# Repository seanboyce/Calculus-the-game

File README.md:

# Introduction
An electronic strategy board game about mining an asteroid and barter. It is also fully compatible with Settlers of Catan. So if you already own that game, you can play it using this board if you wish (using the cards and pieces from the original). The holders of the Catan copyright also generously allow you to make one (1) handmade copy of their game for personal use. A practical thing to do is buy their game, and use the included pieces and cards (although please note the pieces will only physically fit the full-size version, see below). For more information on IP, please visit this link: https://www.catan.com/guidelines-dealing-intellectual-property-catan

Out of respect for their IP (and also for fun), my own game will be sci-fi themed and will not use or refer to their IP beyond this point. 

## Sci-Fi theme?
The name of the game is Calculus, in the sense of a "stone, or concretion of material". In this case, an asteroid in deep space! You are one of up to four corporations that are racing to exploit this valuable asteroid. The corporation that reaches a certain level of development (10 Infrastructure Points) first will own this tiny piece of the sky. This is the object of the game. Besides the four corporations, a mysterious hacker has made their home here, and is bound to interfere with your plans...

(for more information, read the short, bewildering manual)

# Status
The electronics and firmware are in a finished state. Game and reference cards exist and are usable, but the design is nothing special. The game manual is an A5 saddle-stitched booklet, available as a pre-imposed, print-ready document. If you want to help, please redesign my print materials. You are very likely better at this than I am.

There are two versions of this game, both complete:

1. The cheap version (about USD 15.00 to manufacture 1 unit in Asia) -- this version only has one PCB, although you will need 3 units to build the game. It is very cheap to manufacture, but a bit small and cramped to play. Call it a "travel version"! It is missing a little polish overall, and the firmware (while completely functional) is a little chaotic. Notably, trade ports are not electronic (I use magnetic discs), the landing zone (unproductive tile) is limited to being in the center of the board, and there's no MCU on the board itself -- it needs to be added externally and wired in to the inputs. You'll also need to hack in a button. Still, it's very cheap to make and perfectly cromulent.
2. The full-size version (about USD 37.50 to manufacture 1 unit in Asia) -- this one is *much larger* (more than double the size). It uses two PCBs: a large one (you will need 3), and a small one (you will need 1). The small PCB has space for an MCU, making the final board much more self-contained. The small board goes in the center and is also an active game tile -- the landing zone (unproductive tile) can be randomized like other tiles because of this. Trade ports are randomized and represented by RGB LEDs like resource tiles (or off for 3:1). There are also some cosmetic improvements like a proper button and nicer lines. I've also substantially cleaned up the firmware to control all those LEDs -- there are 388 (!) LEDs on the board when you count up all the RGB LEDs and two digit 8-segment displays. 

Other than noted above, both versions play the same. 

## Power
It's expected that you power the game via a USB battery bank. Like the kind you use to recharge phones. However, you can power it from any USB port or 5V source. Current consumption at 5v should be around 250mA for the cheap version, and a little higher for the full version (say 300mA).

Note that some power banks will automatically turn off if the power draw is too low. When pressing the 'next turn' button, the power draw can dip below this threshold, causing the game to turn off and lose it's state! To avoid this, some power banks have a 'low current mode' that disables this feature -- check your powerbank manual.

An alternative solution is to put a resistor across power and ground to increase the current draw. A 100 ohm resistor was sufficient in my case. This adds 50mA to the current consumption, but still keeps it low enough that my power bank will run the game for 30 hours or so per charge.

Building your own rechargeable power supply, or powering it from a phone charger instead of a battery are also reasonable solutions!

## CPU
The cheap version of the game can use more or less any RP2040 based board. The original Pi Pico works fine. The full version specifically requires the XIAO RP2040 -- it's smaller and I needed the space.

## Structural
The boards for the cheap version are intended to be attached above a small project box or similar. This serves the dual purpose of housing a microcontroller, and fixing the 3 PCBs firmly in place. The larger board has all those electronics integrated, and is meant to be bolted to something rigid. I use a circular bamboo serving tray, this leaves a hollow space under the board suitable for storing pieces, the power supply, and the manual.

You can also just add rubber feet to the PCB, the type that are used for furniture and attach on via M3 bolts. This will let you rest it on most flat sufaces. These should be at least 8mm high for proper clearance, I found 10mm more practical. The benefit of this approach is that you can 'stack' the 3 big PCBs, and store the game in a smaller box. On the other hand, it offers no strain relief on the cabling (which can get a bit tangled). I found that bolting it to a rigid surface was much more practical.

## Game Pieces
The cheap requires custom pieces -- hex spacers, bolts, and nuts colored with a permanent marker work fine. The full size board can be played with pieces from a Catan set, or you can make your own.

I like the weight of metal game pieces -- so I dyed 25mm brass hex spacers as the 'tunnels', dyed M6 nuts as the 'mines', and add a ~13mm dyed M6 bolt to them to upgrade them to 'drills'.

To dye these metal pieces, colored permanent marker worked really well.

# Firmware
Besides the assembled PCBs, you will need to load firmware to the main microcontroller (an RP2040). This is pretty easy and can be done over USB. The firmware is heavily commented -- this is so you can make 'house' modifications to the game mechanics, to change the rules if you want. You could even design a completely new game!

# Notes on Assembly
Assembling the PCBs will require that you are comfortable with surface-mount soldering. It's not nearly as hard as it looks. You'll need solder paste and a hot air rework station though. If you don't have these, check if there's a hackerspace near you. They probably will! The default designs use 0402 (1005 metric) components. If you want something easier to solder, look for the 0603 version of the kicad and production files in the fullsize board directory. 

# Having Trouble? Something Confusing?
Raise an issue here on Github. I check in from time to time and will likely respond.

# Image of Completed Board (full version)

# Image of Completed Board (cheap version)

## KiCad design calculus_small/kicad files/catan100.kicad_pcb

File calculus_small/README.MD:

# Pieces
For this game size, brass hex spacers, bolts, and nuts work really well.

- Hex spacers are 'tunnels'
- Nuts are 'mines'
- Nuts with a bolt slightly screwed in are 'drills'

If you color them with permanent marker, they look quite nice.

# Routing
Yeah, the routing on this board is very YOLO. Feel free to make improvements. I have only a few hours of free time per week so optimized for getting the thing done.

# Notes
The production files are in metric units.

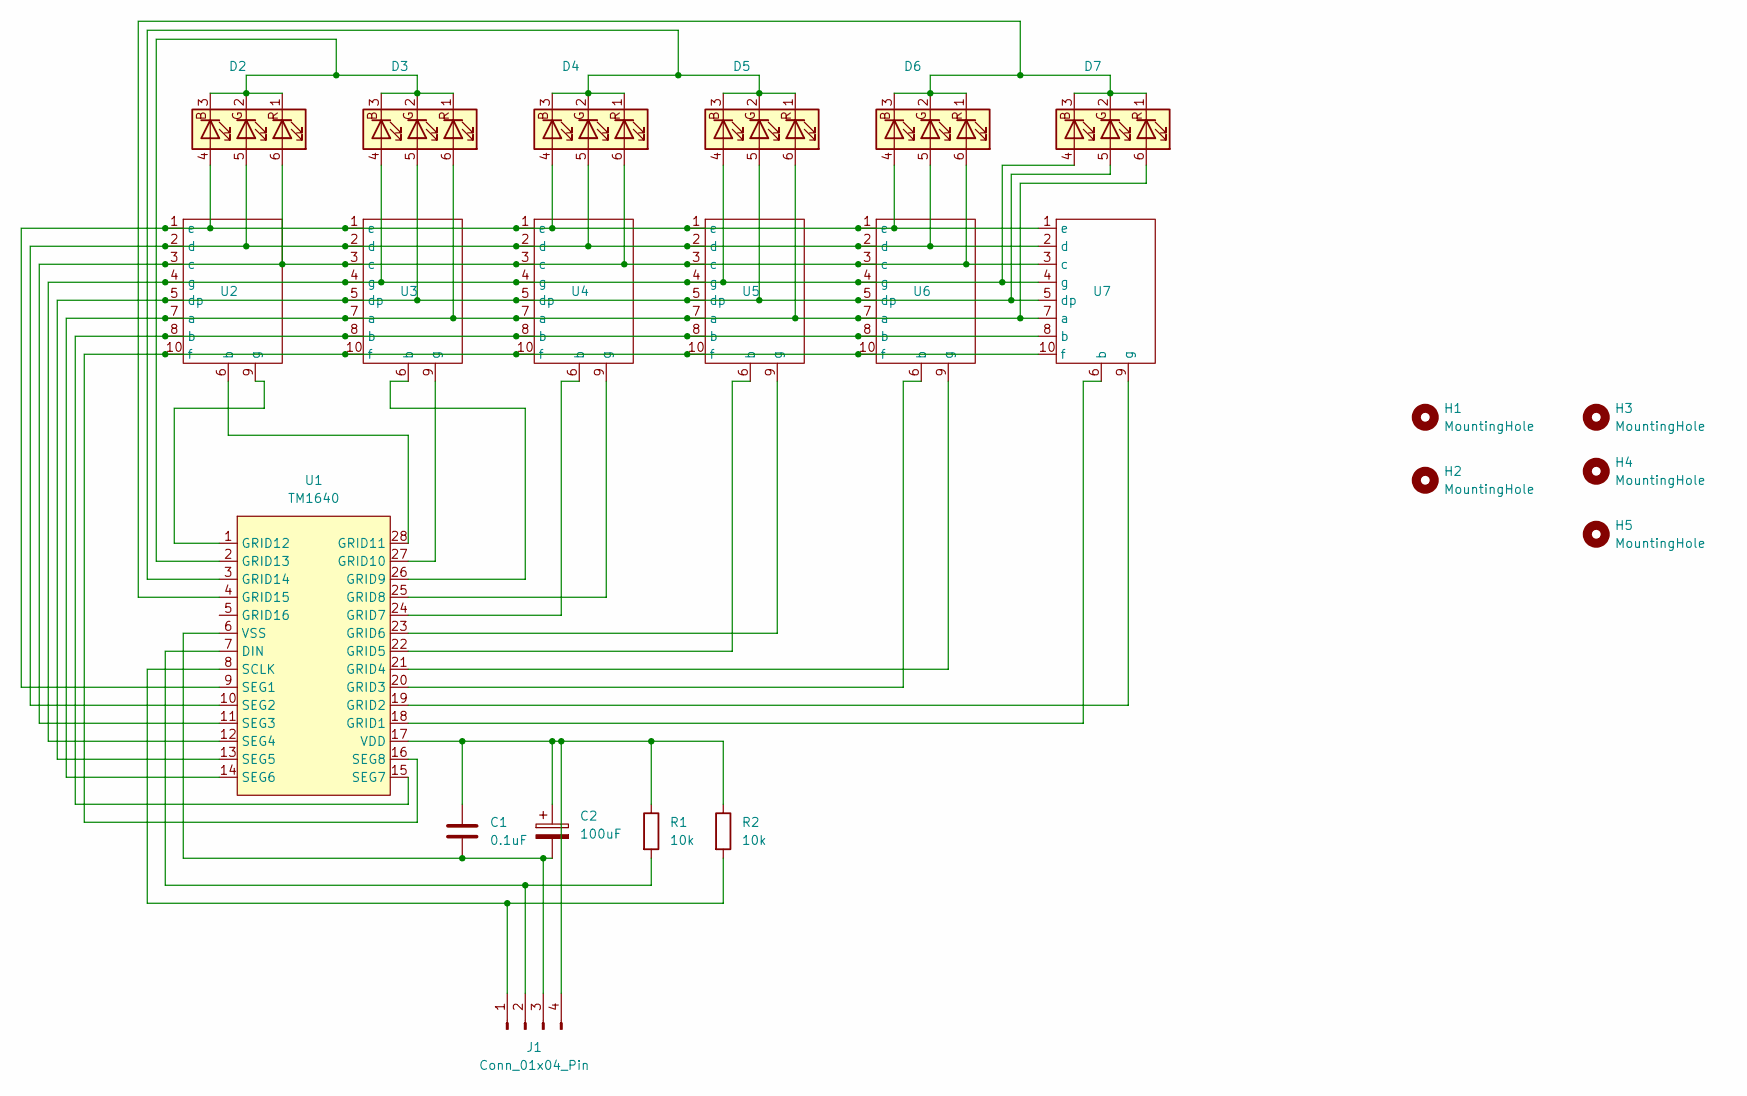
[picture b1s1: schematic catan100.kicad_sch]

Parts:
C1: 0.1uF; C_0603_1608Metric
C2: 100uF; CP_EIA-3528-12_Kemet-T
D1: D2; LED_RGB_5050-6
D2: D3; LED_RGB_5050-6
D3: D4; LED_RGB_5050-6
D4: D5; LED_RGB_5050-6
D5: D6; LED_RGB_5050-6
D6: D7; LED_RGB_5050-6
H1, H2, H3, H4, H5: MountingHole; MountingHole_3.2mm_M3
J1: Conn_01x04_Pin; PinHeader_1x04_P1.27mm_Horizontal
R1, R2: 10k; R_01005_0402Metric
U1: TM1640
U2, U3, U4, U5, U6, U7: 7seg2_small

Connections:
unnamed: D1.4 (BA), D3.4 (BA), D5.4 (BA), U1.9 (SEG1), U2.1 (e), U3.1 (e), U4.1 (e), U5.1 (e), U6.1 (e), U7.1 (e)
unnamed: D1.1 (RK), D1.2 (GK), D1.3 (BK), D2.1 (RK), D2.2 (GK), D2.3 (BK), U1.2 (GRID13)
unnamed: D1.5 (GA), D3.5 (GA), D5.5 (GA), U1.10 (SEG2), U2.2 (d), U3.2 (d), U4.2 (d), U5.2 (d), U6.2 (d), U7.2 (d)
unnamed: D1.6 (RA), D3.6 (RA), D5.6 (RA), U1.11 (SEG3), U2.3 (c), U3.3 (c), U4.3 (c), U5.3 (c), U6.3 (c), U7.3 (c)
unnamed: D2.4 (BA), D4.4 (BA), D6.4 (BA), U1.12 (SEG4), U2.4 (g), U3.4 (g), U4.4 (g), U5.4 (g), U6.4 (g), U7.4 (g)
unnamed: D2.5 (GA), D4.5 (GA), D6.5 (GA), U1.13 (SEG5), U2.5 (dp), U3.5 (dp), U4.5 (dp), U5.5 (dp), U6.5 (dp), U7.5 (dp)
unnamed: D2.6 (RA), D4.6 (RA), D6.6 (RA), U1.14 (SEG6), U2.7 (a), U3.7 (a), U4.7 (a), U5.7 (a), U6.7 (a), U7.7 (a)
unnamed: D3.1 (RK), D3.2 (GK), D3.3 (BK), D4.1 (RK), D4.2 (GK), D4.3 (BK), U1.3 (GRID14)
unnamed: D5.1 (RK), D5.2 (GK), D5.3 (BK), D6.1 (RK), D6.2 (GK), D6.3 (BK), U1.4 (GRID15)
unnamed: J1.1, R2.2, U1.8 (SCLK)
unnamed: J1.2, R1.2, U1.7 (DIN)
unnamed: C1.2, C2.2, J1.3, U1.6 (VSS)
unnamed: C1.1, C2.1, J1.4, R1.1, R2.1, U1.17 (VDD)
unnamed: U1.18 (GRID1), U7.6 (b)
unnamed: U1.19 (GRID2), U7.9 (g)
unnamed: U1.20 (GRID3), U6.6 (b)
unnamed: U1.21 (GRID4), U6.9 (g)
unnamed: U1.22 (GRID5), U5.6 (b)
unnamed: U1.23 (GRID6), U5.9 (g)
unnamed: U1.24 (GRID7), U4.6 (b)
unnamed: U1.25 (GRID8), U4.9 (g)
unnamed: U1.26 (GRID9), U3.6 (b)
unnamed: U1.27 (GRID10), U3.9 (g)
unnamed: U1.28 (GRID11), U2.6 (b)
unnamed: U1.1 (GRID12), U2.9 (g)
unnamed: U1.15 (SEG7), U2.8 (b), U3.8 (b), U4.8 (b), U5.8 (b), U6.8 (b), U7.8 (b)
unnamed: U1.16 (SEG8), U2.10 (f), U3.10 (f), U4.10 (f), U5.10 (f), U6.10 (f), U7.10 (f)

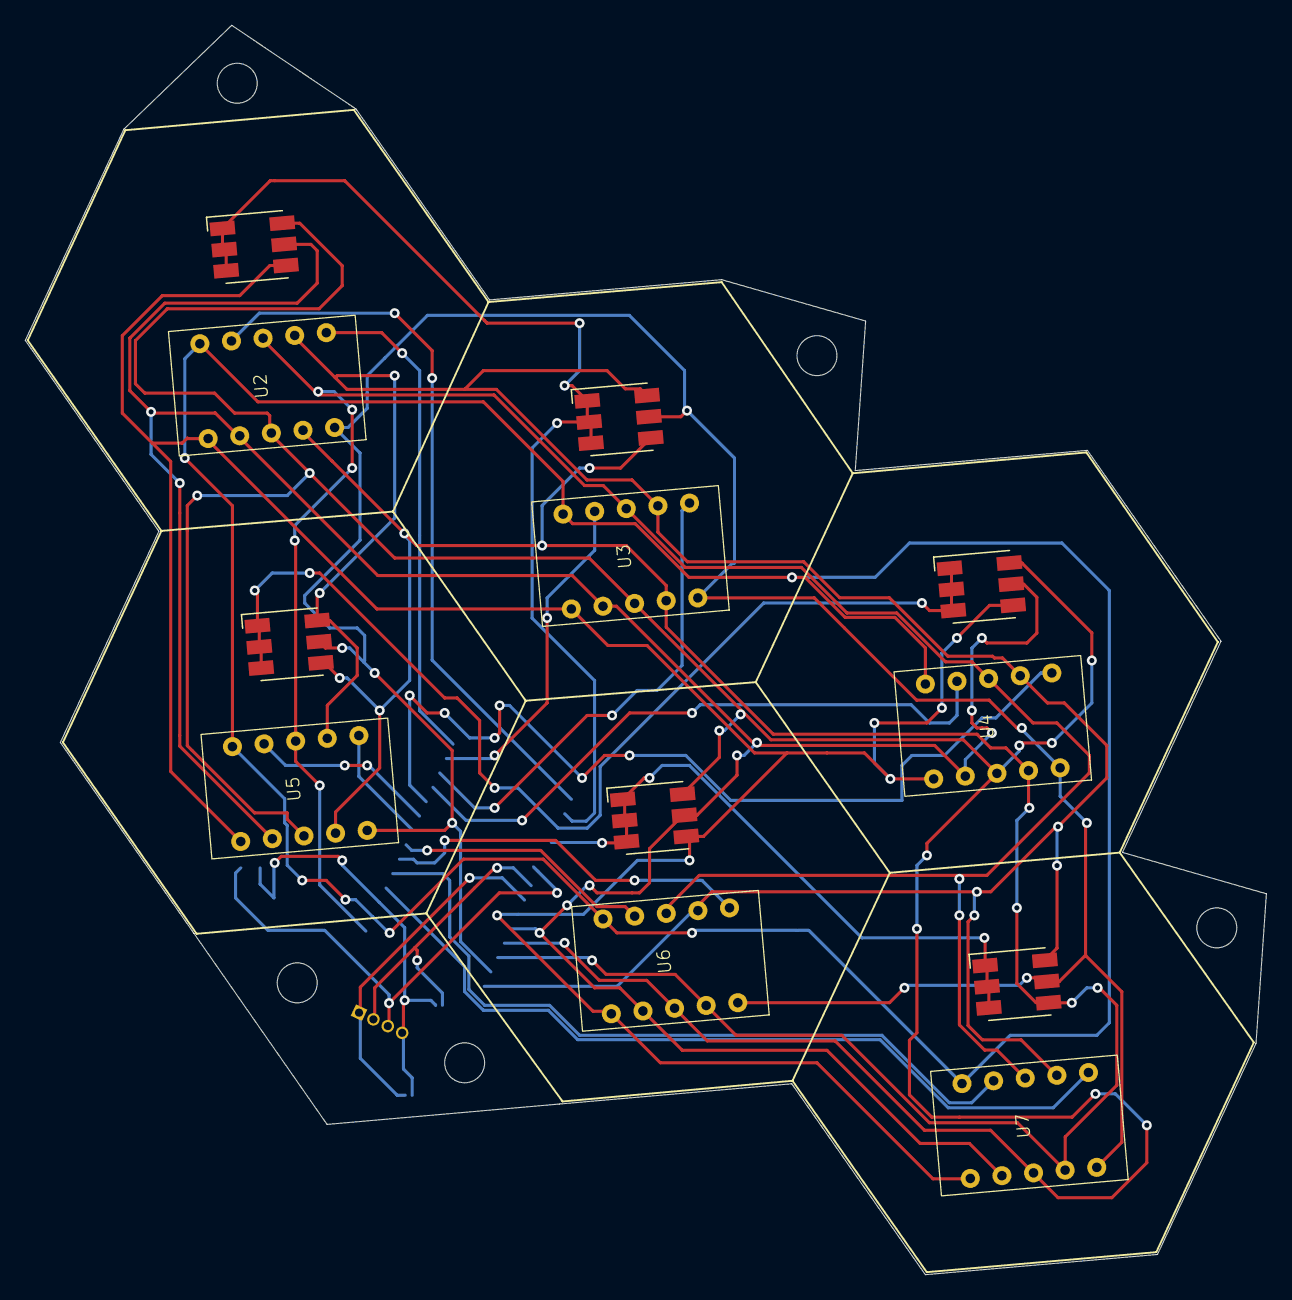
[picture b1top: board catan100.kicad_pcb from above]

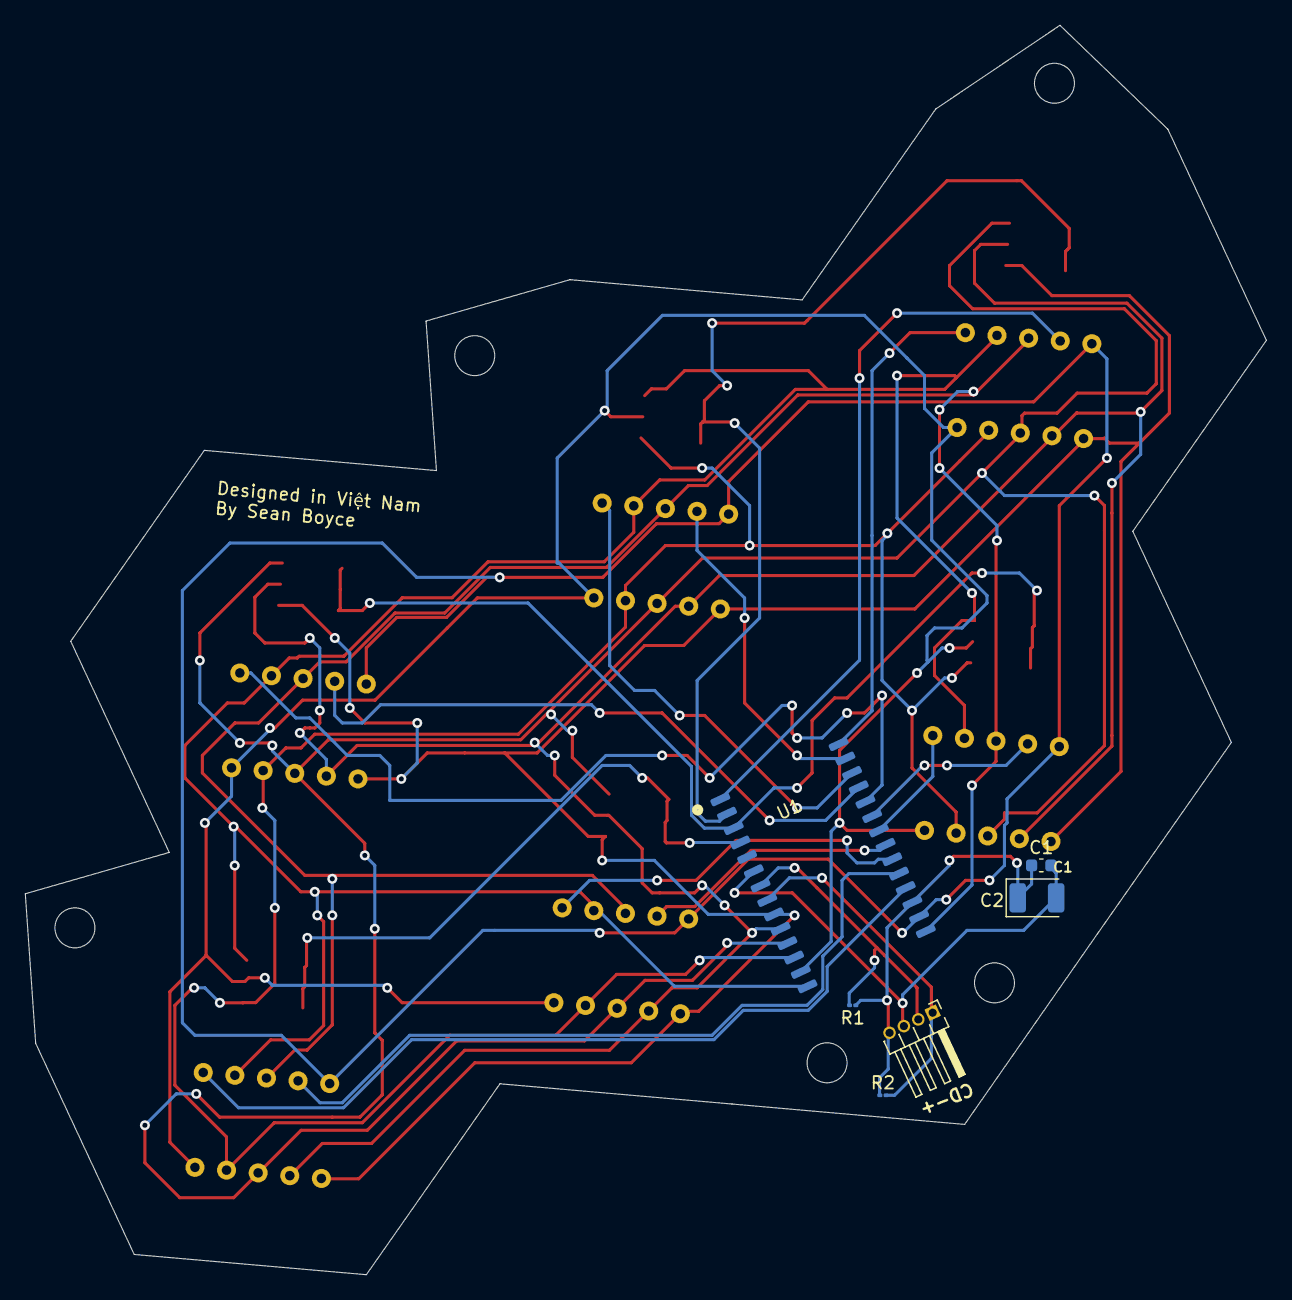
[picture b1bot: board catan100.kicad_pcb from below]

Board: 2 copper layers, 99.3 x 100.0 mm, 23 parts (6 on the bottom side), 27 nets.

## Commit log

2025-03-08 Create LICENSE.md
    Add license
2025-03-08 Add smaller, cheaper version of Calculus
2025-03-08 Add image of completed board
2025-03-17 Create BOM
2025-03-17 Update BOM
2025-04-14 Add files via upload
    Add photos of new board
2025-04-14 Update README.md
    Add some notes on full-size board
2025-04-20 Add files via upload
    Add photography of fully working board
2025-04-20 Add files via upload
    Add Firmware for full version
2025-04-20 Create FIRMWARE.md
    Just minor notes on the firmware
2025-04-20 Add files via upload
    Upload files for production. Note these are metric.
2025-04-20 Delete calculus_full/production files directory
    wrong directory name
2025-04-20 Add files via upload
    add center tile kicad files
2025-04-20 Add files via upload
    add main segment kicad files
2025-04-20 Update and rename BOM to BOM.md
    update BOM
2025-04-20 Rename catan_small.JPG to calculus_small.JPG
2025-04-21 Update README.md
    Add vague idea of cost
2025-04-30 Add files via upload
    Add 0603 (1608 metric) version. This replaces the tiny resistors with larger, easier to solder ones. No other changes besides resistor package size.
2025-06-04 Add files via upload
    Start adding print materials
2025-06-04 Add files via upload
    Add in only sort of bad print materials
2025-06-07 Delete print materials/reference_cards_print_2x.pdf
    Need to fix some text
2025-06-07 Add files via upload
    Fix some text of reference cards
2025-06-07 Add manual
    I wrote a short, bewildering manual. It's main benefit is conspicuously existing, as well as not being absent.
2026-03-14 Add A5 manual PDF
    One option is laid out by page order, the other has the pages imposed for saddle-stitch binding.
2026-03-14 Create README.MD
    Notes on print materials
2026-03-14 Update README.MD
    typo
2026-03-15 Update README.md
    Add notes on USB power bank automatic power off prevention.
2026-03-15 Update README.md
    Add notes about game pieces.
2026-03-15 Update README.md
    Update to include improvements to print materials.
2026-03-15 Update README.md
    Add notes on structural support for the finished boards.
